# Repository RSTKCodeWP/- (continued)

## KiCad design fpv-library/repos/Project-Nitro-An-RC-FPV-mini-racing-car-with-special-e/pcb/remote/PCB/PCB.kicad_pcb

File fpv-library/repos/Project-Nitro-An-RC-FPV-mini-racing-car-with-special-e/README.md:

# Project-Nitro 🏎️💨

### FPV RC Racing Car with Game Effects

Have you ever wondered about having a **FPV RC Racing Car** with game effects such as:
- Boost
- Gun
- Health
- Drift (Bad effects and more)

Well, I have made this with the help of **NFC TAGS**. How it works is simple: when each car has an NFC reader underneath, and when it passes over a NFC tag, it will detect the code and look for what power or bad effect it is. Then I can pull that effect whenever we want. Beat your opponent and win with super powers using our own strategy to win the game!

## Zine
[zine](/doc/zine.pdf)

## Hardware Showcase 🛠️
### Photos of Car and Remote 📸

#### Car 

#### Remote

### Circuit & Diagram

#### Car Schematics

#### Remote PCB & Schematics

## Motivation

I have always wondered to play **RC car** like in games with boost, power, win, health etc.. because that all make more fun for the world and playing with friends makes it even more fun. So I built this car - it will give you a game vibe with RC FPV cars in real life, bringing more fun and joy to the world!
## How to Build 🛠️

### Car Assembly

After 3D printing, check the tolerance of each part and sand it smoothly for better look and placement. Then solder everything with wires, place each component in its designated position as shown in the `.step` files, glue the IR receiver and transmitter, tape or glue the batteries in their places, place ESP32 on the ESP tray and screw it well, then mount to the car body as shown.
## Car Assembly

1. 3D print all STL files from `/cad/car`.
2. Sand the parts until they fit smoothly.
3. Insert all M3 heat inserts
4. Mount the N20 motor using two M3 screws.
5. Install the steering servo.
6. Mount the ESP32.
7. Install the PN532 NFC module.
8. Connect all electronics according to wiring diagram.
9. Mount FPV cam.
10. Install battery
11. scraw body

### Remote Assembly
## Car Assembly

1. 3D print all STL files from `/cad/remote`.
2. Sand the parts until they fit smoothly.
3. Insert all M3 heat inserts.
4. place the batter.
5. Mound the ESP32.
6. Mount PCB after soldering all switchs and LED.
7. Insert the button.
8. Connect all electronics according to wiring diagram.
9. Slide in the sreen and screw.
10. Slide the bottom case.
11. Close body.

After 3D printing, check the tolerance of each part and sand it smoothly for better look and placement. Then solder everything with wires, place the battery first followed by ESP32, solder the switch to PCB and connect the GPIOs Don't forget to place the LCD screen holders to screw for better holding, slide down the bottom part and screw it also then paint everything.

## How to Play/Setup 🎮

When you turn on the remote and car, it will connect (if it's your first time,you may need to pair them) You'll get a web interface in phone or laptop for FPV. Once connected you have two modes:

### Free Ride Mode
You can drive it as normal RC car without any special features.

### Race Mode  
In this mode, you need an opponent to play with. One of you will host the game and that person's car becomes the controller of the game also. The remote looks for players  when a player is found:
- Flip the car and reegister all NFC tags again
- Accept the win gate tag and pit lane
- Place everthing in place as you want
- Everywhere, you can make your own track with anything you have
- Play and win the game
## Game Effects ⚡

### Good Power-ups
- **Boost** - Speed boost to move faster  
- **Health** - Get more health  
- **Shield** - Protection from enemy bullets  
- **Bullets** - Shoot projectiles  

### Bad Effects
- **Drift** - The car gets drift randomly  
- **Random Control** - Controls switch randomly (forward becomes backward)  
- **Slowness** - Car goes slowly  
- **Damage** - Low health  

### Bonus Feature
All bad effects can be cleared by going to your own pit lane.
## How It Works ⚙️

This all works with ESP-NOW protocol. The host's car maintains the rules and everything:

- `car ↔ remote` - Direct communication between each unit  
- `car(host) ↔ car(client)` - Host communicates with client cars  
- `camera → WiFi web → phone, laptop...` - Video stream to viewer devices

## Folder Structure 📁
```
cad/

├── car/
│   └── car.step

├── remote/
│   └── Remote.step

├── nfc/
│   └── nfc tag sticker.step

firmware/

├── car/
│   └── Car firmware

├── remote/
│   └── Remote firmware

├── camera/
│   └── FPV camera firmware
```

### Car Section
- [Car CAD](/cad/car/) - 3D models and designs  
- [Car Firmware](/firmware/car/) - Embedded code for the Car  
- [FPV Camera](/firmware/car_cam/) - Camera firmware  
- [Car Circuit](/circuit/car/) - Schematic diagrams  

### Remote Section
- [Remote CAD](/cad/remote/) - 3D models and designs  
- [Remote Firmware](/firmware/remote/) - Embedded code for the remote  
- [Remote circuit](/circuit/remote/) - Schematic diagrams

## BOM (Bill of Material)
[BOM](/doc/BOM.csv.csv)

## Car Components 🛒

|**Item**|Number|Approx. Price|Link|
|--------|-------------|-------------|---|
|5mm 940nm IR Emitter Transmitter|2|₹140|[Amazon](https://amzn.in/d/03gj3whx)|
|MPU6050 IMU|1|₹174|[Amaz](https://amzn.in/d/0gS9H64g)|
|PN532 NFC RFID Module|1|₹425|[Robokit](https://robokits.co.in/wireless-solutions/rfid/pn532-nfc-rfid-module-v3-kit-reader-writer-breakout-board?srsltid=AfmBOooBJS2DFnuWBIGC9mB0mO7za8Ql3MFEb6kDh34OEwg5jFQdKodmrjA)|
|ESP32S3-Sense|1|₹1800|[SeeedStudio](https://www.seeedstudio.com/XIAO-ESP32S3-Sense-p-5639.html?srsltid=AfmBOooVpv6VY6S8HZ8RSQHJR3o-OCpF9PW-xqElodKlTDqwqZxqCzhl)|
|ESP32 WiFi Bluetooth|1|₹299|[Amazon](https://amzn.in/d/0fkaqaUV)|
|6V N20 600 RPM Motor|1|₹149|[Robocraz](https://robocraze.com/products/6v-n20-600-rpm-miniature-gear-motor)|
|3.7V 2500mAh 18650 Li-Ion Battery|2|₹500|[Robocraze](https://robocraze.com/products/3-7v-2500mah-18650-li-ion-battery)|
|TP4056 Type-C Mini Charger|1|₹49|[Robocraz](https://robocraze.com/products/tp4056-battery-charger-c-type-module-with-protection-1)|
|LM2596 DC-DC Buck Converter|1|₹79|[Robocraze](https://robocraze.com/products/lm2596-dc-dc-buck-module)|
|SG90 Micro Servo Motor|1|₹99|[robocraze](https://robocraze.com/products/sg90-micro-servo-motor)|
|DRV8833 2-Channel Driver|1|₹99|[Robocraze](https://robocraze.com/products/drv8833-2-channel-dc-motor-driver)|
|TSOP38238 IR Receiver Diode|2|₹50|[QuartzComponents](https://quartzcomponents.com/products/tsop38238-ir-receiver-diode-38khz)|
|M3x4mm Heat Set Inserts|20|₹80|[Robu](https://robu.in/product/m3-x-4-mm-brass-heat-set-knurl-threaded-round-insert-nut-25-pcs/)|
|M3 x 6mm Screw|20|₹60|[RoboticsDNA](roboticsdna.in/product/m3-x-6mm-bolt-ss-304-csk-countersunk-philips-head-25-pcs/)|

#### Approximate Car Cost: **₹4,000**

### Remote

|**Item**|Number|Approx. Price|Link|
|--------|-----|-------------|---|
|ESP32 WiFi Bluetooth|1|₹299|[Amazon](https://amzn.in/d/03HUoLg3)|
|Tactile momentary push button|12|₹36|[amazon](https://amzn.in/d/093r9Vyk)|
|3.7V 1500mAh LiPo Rechargeable Battery Model|1|₹350|[robocraze](https://robocraze.com/products/3-7v-1500mah-lipo-rechargeable-battery-model-uk-523450p?_pos=1&_sid=d113ab62b&_ss=r)|
|TP4056 Type-C Mini|1|₹49|[robocraze](https://robocraze.com/products/tp4056-battery-charger-c-type-module-with-protection-1)|
|3.3V Small Piezo Buzzer|1|₹30|https://robocraze.com/products/3-volts-buzzer-small|
|5mm Common Anode RGB LED 4Pin Through Hole White Diffused LED|1|₹15|[robocraze](https://robocraze.com/products/5mm-common-anode-rgb-led-4pin-pack-of-10)|
|2.8 Inch TFT LCD Display|1|₹780|[robocraze](https://robocraze.com/products/smartelex-2-8-inch-tft-lcd-display-240x320-color-lcd-screen-for-diy-electronics)|
|m3x4mm heat set inserts|12|₹80|[Rubu](https://robu.in/product)|m3-x-4-mm-brass-heat-set-knurl-threaded-round-insert-nut-25-pcs/|
|M3 x 6mm screw|12|₹60|[RoboticsDNA](roboticsdna.in/product/m3-x-6mm-bolt-ss-304-csk-countersunk-philips-head-25-pcs/)
#### Approximate Remote Cost
**₹1700**

### Total Approximate Cost

|Part|Cost|
|-----|-----|
|Car|₹4000|
|Remote|₹1700|

# Future Upgrade ⏫

* Leader Board 
* Anti-Cheat
* challenge etc

Thats it for now.
> **NOTE:** you need to place a black transparent plastic thin sheet or something on the front window where the camera is placed and in the remote for the switch you can either use this Prototyping PCB or you can custom print a pcb board everything on car and remote is either snap fit or screwable and only the led , ir and batter need glue-gun/tap

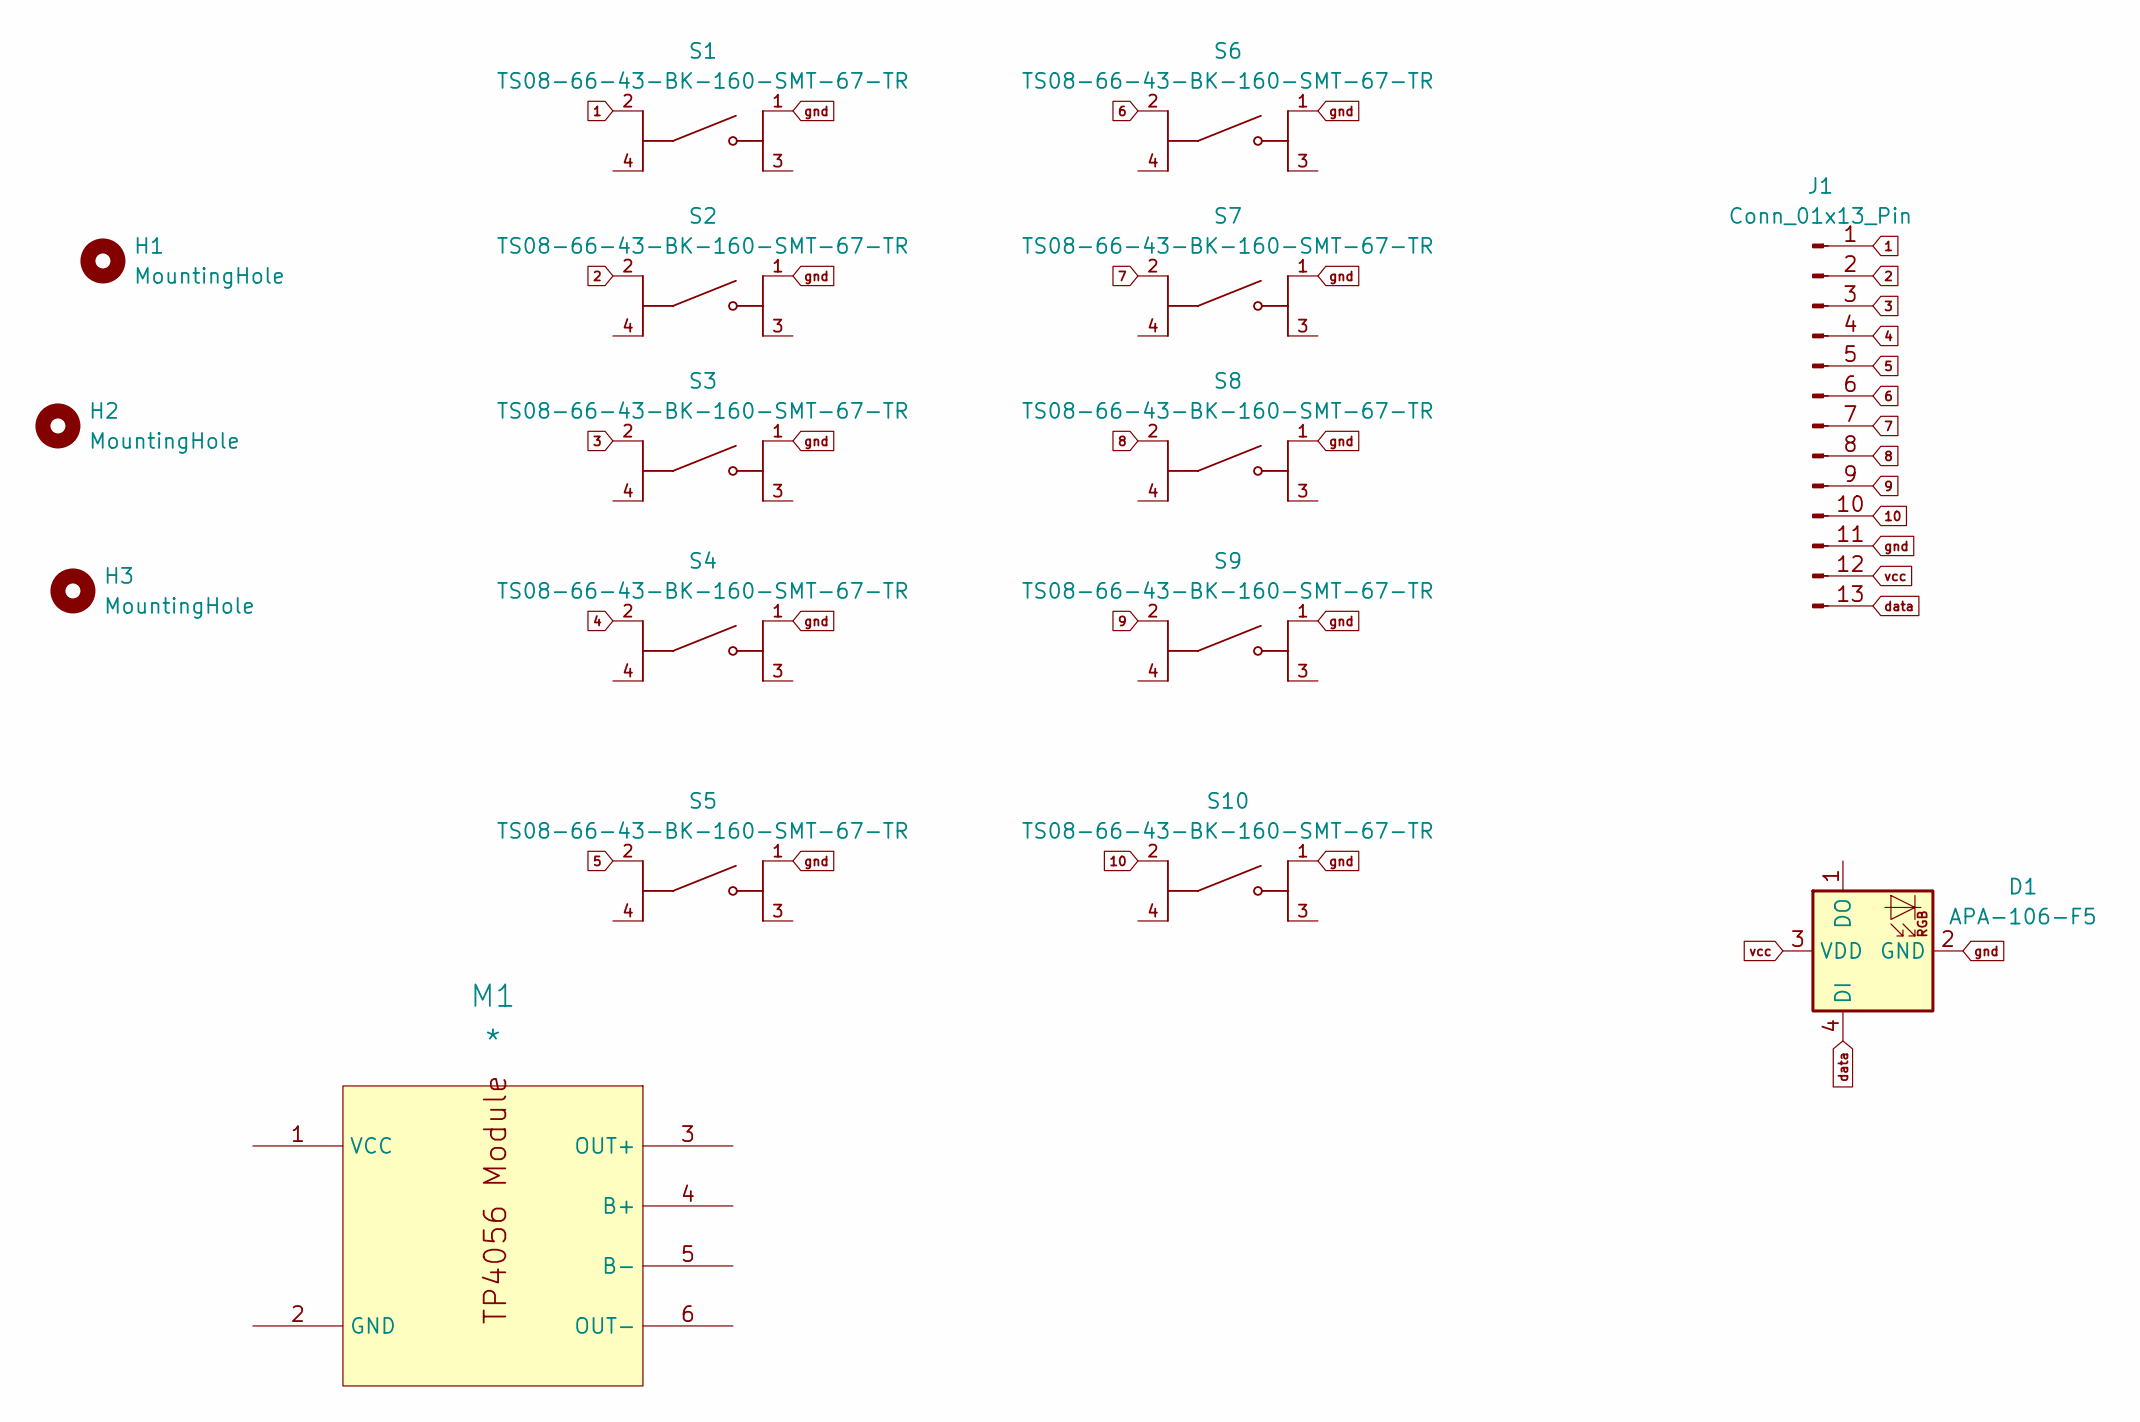
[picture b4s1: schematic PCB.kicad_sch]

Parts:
D1: APA-106-F5; LED_D5.0mm-4_RGB
H1, H2, H3: MountingHole; MountingHole_3mm
J1: Conn_01x13_Pin; PinSocket_1x13_P2.00mm_Horizontal
M1: *; tp4056
S1, S2, S3, S4, S5, S6, S7, S8, S9, S10: TS08-66-43-BK-160-SMT-67-TR; SW_PUSH_6mm; PARTREV 1.03

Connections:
1: J1.1, S1.2
2: J1.2, S2.2
3: J1.3, S3.2
4: J1.4, S4.2
5: J1.5, S5.2
6: J1.6, S6.2
7: J1.7, S7.2
8: J1.8, S8.2
9: J1.9, S9.2
10: J1.10, S10.2
data: D1.4 (DI), J1.13
gnd: D1.2 (GND), J1.11, S1.1, S2.1, S3.1, S4.1, S5.1, S6.1, S7.1, S8.1, S9.1, S10.1
vcc: D1.3 (VDD), J1.12

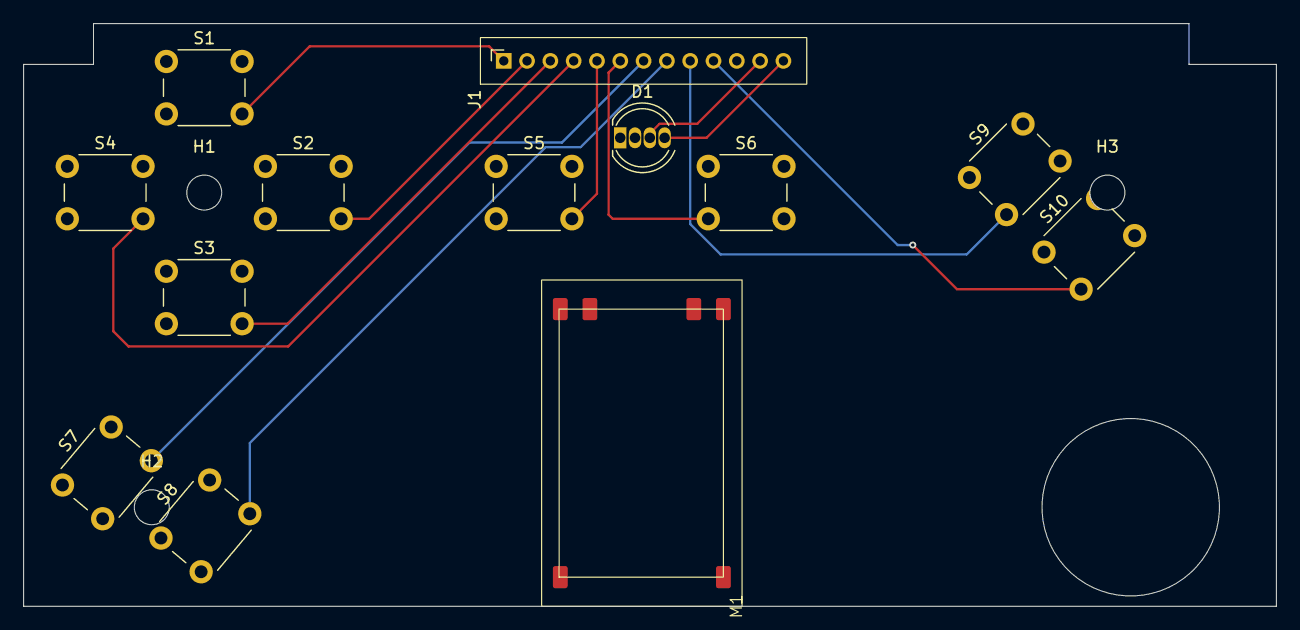
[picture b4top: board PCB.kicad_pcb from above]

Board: 2 copper layers, 107.5 x 50.0 mm, 16 parts (0 on the bottom side), 13 nets.

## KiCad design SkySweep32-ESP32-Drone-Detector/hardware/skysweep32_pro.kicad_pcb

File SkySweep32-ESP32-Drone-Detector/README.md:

# SkySweep32 | Пассивный детектор БПЛА

**Multi-band passive drone detector | Мультидиапазонный пассивный детектор дронов**

[English](#english) | [Русский](#russian)

---

## 🇬🇧 English

### Overview

SkySweep32 is an advanced passive drone detection system based on the ESP32 microcontroller. It monitors radio spectrum across three frequency bands (900 MHz, 2.4 GHz, 5.8 GHz) to detect UAV control signals and video transmission. **Built with a modular, budget-friendly architecture** — start with a ~$15 base kit and upgrade as needed.

### 📦 Modular Tiers

| Tier | Name | Cost | Includes |
|------|------|------|----------|
| 🟢 **Base** | Starter | ~$15-20 | ESP32 + OLED + NRF24L01+ (2.4 GHz) + Web Dashboard + BLE Remote ID |
| 🟡 **Standard** | Hunter | ~$35-45 | Base + CC1101 (900 MHz) + RX5808 (5.8 GHz) + ML Classification |
| 🔴 **Pro** | Sentinel | ~$60-80 | Standard + GPS + SD Card Logger + LoRa Mesh Network |
| 🟣 **EW Mode** | Juggernaut | ~$100+ | Sentinel + 4x VCO Jamming Modules (5.8G, 2.4G, 900M, 1.5G) |

**Optional add-ons**: 🎤 Acoustic Detection (~$5) | ⚔️ Countermeasures (auth required)

> 📖 **[Full Modular Guide →](docs/en/modules.md)**

### Features

- **Multi-band RF & Spectrum Scanning**: Hardware sweeping across 900 MHz, 2.4 GHz, and 5.8 GHz bands checking for analog and digital drone links.
- **Web Dashboard & Map**: Real-time dark-themed dashboard via WiFi with Leaflet.js interactive map, drone lists, and RSSI graphs.
- **Signal Fingerprinting**: Built-in `SignalDatabase` identifying known drone patterns (e.g., DJI OcuSync, FPV Analog, Crossfire) via band-matching and RSSI variance.
- **ESP-NOW Mesh**: Free, autonomous node-to-node network sharing threat alerts, heartbeats, and GPS telemetry across massive areas without extra hardware.
- **Power Management**: 4 dynamic power states (Full, Balanced, Low, Deep Sleep) with battery ADC monitoring and runtime estimates.
- **Countermeasures (Juggernaut)**: Optional VCO signal injection covering DJI, Walksnail, OpenIPC, ELRS, and GPS Denial.
- **ATAK Integration (Cursor on Target)**: Native UDP broadcast of CoT packets to the Android Team Awareness Kit, showing drone targets and operator heading on tactical maps.
- **Hardware Compass (QMC5883L)**: Direction finding via I2C magnetometer, calculating the vector of incoming drone signals.
- **TinyML AI Classification**: TensorFlow Lite for Microcontrollers engine for predicting drone classes (DJI, FPV, etc.) based on RSSI variance and multi-band tensors.
- **Stealth Mode (Dark Mode)**: Hardware/Software toggle to instantly disable OLED and buzzers, transferring all alerts to a covert vibration motor.
- **Auto-Calibration Tool**: Integrated baseline noise calibration directly from the Web-UI.
- **Alert System**: Non-blocking intelligent Buzzer and LED patterns scaling with Threat Levels (Info → Critical).
- **Remote ID**: FAA ANSI/CTA-2063 compliant BLE drone identification natively on the ESP32.
- **FreeRTOS Architecture**: Safe concurrent processing with hardware Watchdogs and SPI mutexes.

### Hardware Components (Standard Tier)

| Component | Model | Frequency | Purpose |
|-----------|-------|-----------|---------| 
| Microcontroller | ESP32 DevKit | - | Main processor + WiFi + BLE |
| RF Module 1 | CC1101 | 900 MHz | ISM band monitoring |
| RF Module 2 | NRF24L01+ | 2.4 GHz | WiFi/RC monitoring |
| RF Module 3 | RX5808 | 5.8 GHz | Video link monitoring |
| Display | OLED 128x64 (I2C) | - | Visual interface |
| Microphone (optional) | ICS-43434 MEMS | I2S | Acoustic detection |

> 🛠️ **Ready to Build?**
> See the [PCB Assembly Guide (Pro Tier)](docs/en/pcb_assembly.md) for full BOM, KiCad files, and soldering instructions.
> Looking for a case? We have official FreeCAD/STL designs in the [Enclosures Guide](docs/en/enclosures.md).

### Pinout Configuration (Conflict-Free)

#### SPI Bus (Shared)
| Signal | ESP32 Pin |
|--------|-----------|
| MOSI   | GPIO 23   |
| MISO   | GPIO 19   |
| SCK    | GPIO 18   |

#### Chip Select Pins
| Module      | CS Pin    | CE Pin | Tier |
|-------------|-----------|--------|------|
| NRF24L01+   | GPIO 15   | GPIO 2 | Base+ |
| CC1101      | GPIO 5    | -      | Standard+ |
| RX5808      | GPIO 13   | -      | Standard+ |
| LoRa SX1276 | GPIO 14   | -      | Pro (Changed in v0.4) |
| SD Card     | GPIO 27   | -      | Pro |

#### EW Output Pins (Juggernaut)
| Signal | ESP32 Pin | Purpose |
|--------|-----------|---------|
| DAC 1  | GPIO 25   | 5.8GHz / 2.4GHz VCO Sweep |
| DAC 2  | GPIO 26   | 900MHz / 1.5GHz GPS VCO Sweep |
| LORA_R | GPIO 12   | LoRa Reset moved here |

#### I2C Bus (OLED Display)
| Signal | ESP32 Pin |
|--------|-----------|
| SDA    | GPIO 21   |
| SCL    | GPIO 22   |

#### Additional Connections
- **RX5808 RSSI**: GPIO 34 (ADC1_CH6)
- **Power**: 3.3V and GND to all modules

### Software Architecture

```
src/
├── main.cpp                    # FreeRTOS tasks & app orchestration
├── config.h                    # Central config: tiers, pins, feature flags
├── config_manager.h/cpp        # Runtime JSON config (SPIFFS)
├── spi_manager.h/cpp           # Thread-safe shared-SPI bus (mutex)
├── power_manager.h/cpp         # Power modes, battery ADC, deep sleep
├── alert_manager.h/cpp         # Non-blocking buzzer/LED alert patterns
├── countermeasures.h/cpp       # Threat assessment + optional EW (Juggernaut)
├── signal_database.h/cpp       # Drone signal fingerprinting
├── espnow_mesh.h/cpp           # ESP-NOW node-to-node mesh alerts
├── web_server.h/cpp            # WiFi AP, dashboard, REST + WebSocket
├── remote_id_detector.h/cpp    # BLE Remote ID scanner
├── ml_classifier.h/cpp         # Drone classification (rules + TFLite)
├── model_data.h                # TinyML model blob
├── gps_module.h/cpp            # GPS (NEO-6M/7M)            [Pro]
├── data_logger.h/cpp           # SD-card forensic logging   [Pro]
├── meshtastic_client.h/cpp     # LoRa mesh + trilateration  [Pro]
├── atak_client.h/cpp           # ATAK Cursor-on-Target UDP  [optional]
├── compass_module.h/cpp        # QMC5883L direction finding [optional]
├── acoustic_detector.h/cpp     # I2S MEMS acoustic detection[optional]
├── drivers/
│   ├── cc1101.h/cpp            # CC1101 900 MHz driver
│   ├── nrf24l01.h/cpp          # NRF24L01+ 2.4 GHz driver
│   └── rx5808.h/cpp            # RX5808 5.8 GHz driver
└── protocols/
    ├── mavlink_parser.h/cpp    # MAVLink protocol decoder
    └── crsf_parser.h/cpp       # CRSF/ExpressLRS decoder

test/host/                      # Desktop unit tests (g++ + ASan/UBSan)
```

### Build Instructions

```bash
# Clone repository
git clone https://github.com/bobberdolle1/SkySweep32.git
cd SkySweep32

# Build firmware
pio run

# Upload to ESP32
pio run --target upload

# Monitor serial output
pio device monitor
```

### Testing

The protocol parsers (CRSF/MAVLink), which decode untrusted over-the-air input, have
desktop unit tests that build with the host `g++` — no ESP32 toolchain required:

```bash
make -C test/host      # builds with AddressSanitizer/UBSan and runs the suite
```

These run in CI (`.github/workflows/host-tests.yml`) alongside a `cppcheck`
static-analysis pass. See [`test/host/README.md`](test/host/README.md).

### Configuration

#### Enable Countermeasures (REQUIRES LEGAL AUTHORIZATION)

Edit `platformio.ini`:
```ini
build_flags = -DENABLE_COUNTERMEASURES
```

Edit `src/main.cpp`:
```cpp
counterMeasures.armSystem(true);  // Uncomment this line
```

### Legal Notice

⚠️ **WARNING**: Active RF countermeasures (jamming, protocol injection) are **ILLEGAL** in most jurisdictions without explicit authorization from regulatory authorities. Use of these features may result in:

- Criminal prosecution
- Heavy fines
- Equipment confiscation
- Interference with critical communications

**Authorized Use Cases**:
- Military and law enforcement operations
- Critical infrastructure protection (with permits)
- Conflict zones with appropriate authorization
- Research and development in controlled environments

**This project is for educational and authorized defense purposes only.**

### Documentation

- 🍼 **[Absolute Beginner Guide (Start Here)](docs/en/start_from_zero.md)** — No soldering, Lego-style assembly for beginners
- 📘 [Hardware Setup Guide](docs/en/hardware.md) — Advanced wiring & BOM
- 💻 [Software API Reference](docs/en/software.md) — REST & WebSocket APIs
- ⚖️ [Legal Compliance](docs/en/legal.md) — Responsible use

### License

GNU General Public License v3.0 - See [LICENSE](LICENSE) file for details.

---

## 🇷🇺 Русский

### Обзор

SkySweep32 — продвинутая система пассивного обнаружения дронов на базе микроконтроллера ESP32. Система мониторит радиоэфир в трех диапазонах (900 МГц, 2.4 ГГц, 5.8 ГГц) для детекции сигналов управления БПЛА и видеопередачи. Включает опциональные возможности активного противодействия для авторизованных оборонных применений.

### Возможности

- **Мультидиапазонное и Спектральное сканирование**: Аппаратный скан эфира на 900 МГц, 2.4 ГГц и 5.8 ГГц диапазонах для детекции пультов, телеметрии и видеолинков.
- **Web-Дашборд и Интерактивная Карта**: Локальный веб-интерфейс по WiFi с картой (Leaflet.js) для трекинга дронов и операторов через Remote ID.
- **Сигнатурная База (Fingerprinting)**: Динамическое распознавание 8 типов дронов (DJI OcuSync, FPV, Crossfire и др.) через анализ дисперсии RSSI и паттернов "прыжков".
- **Своя Mesh-сеть (ESP-NOW)**: Самоорганизующаяся децентрализованная сеть оповещения между детекторами (0 рублей стоимости, использует WiFi чип ESP32).
- **Активный РЭБ (Juggernaut)**: Управление каскадом из 4-х внешних VCO-генераторов (5.8GHz, 2.4GHz, 900MHz, 1.5GHz GPS) через DAC-пины для подавления DJI, Walksnail, BetaFPV, OpenIPC и ELRS.
- **Power Management (Батарея)**: Глубокий сон, скалер частоты ЦП и ADC-отслеживание батареи. Позволяет работать от 18650 днями. Автоматическая калибровка шума из UI.
- **Умная Система Уведомлений**: Неблокирующий диспетчер сигналов для зуммера (Buzzer) и LED с динамическими паттернами под каждый уровень угрозы.
- **Оценка угроз**: 5-уровневая классификация (НЕТ/НИЗКАЯ/СРЕДНЯЯ/ВЫСОКАЯ/КРИТИЧЕСКАЯ).
- **Активное противодействие (опционально, требуется легальная авторизация)**.

### Компоненты (Уровень Hunter)

| Компонент | Модель | Частота | Назначение |
|-----------|--------|---------|------------|
| Микроконтроллер | ESP32 DevKit | - | Основной процессор + WiFi/BLE |
| РЧ-модуль 1 | CC1101 | 900 МГц | Мониторинг ISM-диапазона |
| РЧ-модуль 2 | NRF24L01+ | 2.4 ГГц | Спектральное сканирование / RC |
| РЧ-модуль 3 | RX5808 | 5.8 ГГц | Мониторинг видеолинка |
| Дисплей | OLED 128x64 | - | Визуальный интерфейс |
| Индикация | Passive Buzzer | - | Алерты и ошибки |

> 🛠️ **Готовы к сборке?**
> Смотрите [Руководство по сборке платы (Pro Tier)](docs/ru/pcb_assembly.md) — там полный список деталей (BOM), KiCad проекты и инструкции по пайке.
> Ищете корпус? Официальные 3D-модели (STL) и чертежи находятся в [Руководстве по корпусам](docs/ru/enclosures.md).

### Распиновка (Бесконфликтная)

#### Шина SPI (общая)
| Сигнал | Пин ESP32 |
|--------|-----------|
| MOSI   | GPIO 23   |
| MISO   | GPIO 19   |
| SCK    | GPIO 18   |

#### Пины Chip Select (индивидуальные)
| Модуль      | CS пин    | CE пин (если есть) |
|-------------|-----------|--------------------|
| NRF24L01+   | GPIO 15   | GPIO 2             |
| CC1101      | GPIO 5    | -                  |
| RX5808      | GPIO 13   | -                  |
| LoRa SX1276 | GPIO 14   | -                  |
| SD Card     | GPIO 27   | -                  |

#### Пины генерации помех (Уровень Juggernaut)
| Пин | Функция | 
|-----|---------|
| GPIO 25 | DAC 1 (Шум для 5.8GHz и 2.4GHz VCO) |
| GPIO 26 | DAC 2 (Шум для 900MHz и 1.5GHz GPS VCO) |
| GPIO 12 | LoRa RESET (перенесен с GPIO 25) |

#### Шина I2C (OLED-дисплей)
| Сигнал | Пин ESP32 |
|--------|-----------|
| SDA    | GPIO 21   |
| SCL    | GPIO 22   |

#### Дополнительные подключения (Питание и Алерты)
- **Зуммер (Buzzer)**: GPIO 4
- **LED оповещения**: GPIO 2
- **ADC Батареи (100k/100k)**: GPIO 36
- **RX5808 RSSI**: GPIO 34 (ADC1_CH6)
- **Питание**: 3.3V и GND на все модули (регулятор LDO 1117 обязателен!)

### Архитектура ПО

```
src/
├── main.cpp                    # Задачи FreeRTOS и оркестрация приложения
├── config.h                    # Центральный конфиг: уровни, пины, флаги функций
├── config_manager.h/cpp        # Runtime JSON-конфиг (SPIFFS)
├── spi_manager.h/cpp           # Потокобезопасная общая шина SPI (мьютекс)
├── power_manager.h/cpp         # Режимы питания, ADC батареи, глубокий сон
├── alert_manager.h/cpp         # Неблокирующие паттерны зуммера/LED
├── countermeasures.h/cpp       # Оценка угроз + опциональный РЭБ (Juggernaut)
├── signal_database.h/cpp       # Сигнатурная база дронов
├── espnow_mesh.h/cpp           # Mesh-оповещения ESP-NOW между узлами
├── web_server.h/cpp            # WiFi AP, дашборд, REST + WebSocket
├── remote_id_detector.h/cpp    # Сканер BLE Remote ID
├── ml_classifier.h/cpp         # Классификация дронов (правила + TFLite)
├── model_data.h                # Блоб модели TinyML
├── gps_module.h/cpp            # GPS (NEO-6M/7M)             [Pro]
├── data_logger.h/cpp           # Логирование на SD-карту     [Pro]
├── meshtastic_client.h/cpp     # LoRa mesh + трилатерация    [Pro]
├── atak_client.h/cpp           # ATAK Cursor-on-Target UDP   [опц.]
├── compass_module.h/cpp        # QMC5883L пеленгация          [опц.]
├── acoustic_detector.h/cpp     # Акустика I2S MEMS            [опц.]
├── drivers/
│   ├── cc1101.h/cpp            # Драйвер CC1101 900 МГц
│   ├── nrf24l01.h/cpp          # Драйвер NRF24L01+ 2.4 ГГц
│   └── rx5808.h/cpp            # Драйвер RX5808 5.8 ГГц
└── protocols/
    ├── mavlink_parser.h/cpp    # Декодер протокола MAVLink
    └── crsf_parser.h/cpp       # Декодер CRSF/ExpressLRS

test/host/                      # Юнит-тесты на хосте (g++ + ASan/UBSan)
```

### Инструкции по сборке

```bash
# Клонировать репозиторий
git clone https://github.com/bobberdolle1/SkySweep32.git
cd SkySweep32

# Собрать прошивку
pio run

# Загрузить на ESP32
pio run --target upload

# Мониторинг Serial
pio device monitor
```

### Тестирование

Парсеры протоколов (CRSF/MAVLink), разбирающие недоверенный ввод из эфира, покрыты
юнит-тестами, которые собираются хостовым `g++` — тулчейн ESP32 не нужен:

```bash
make -C test/host      # сборка с AddressSanitizer/UBSan и запуск тестов
```

Они гоняются в CI (`.github/workflows/host-tests.yml`) вместе со статическим
анализом `cppcheck`. Подробнее — [`test/host/README.md`](test/host/README.md).

### Конфигурация

#### Включение противодействия (ТРЕБУЕТСЯ ЛЕГАЛЬНАЯ АВТОРИЗАЦИЯ)

Редактировать `platformio.ini`:
```ini
build_flags = -DENABLE_COUNTERMEASURES
```

Редактировать `src/main.cpp`:
```cpp
counterMeasures.armSystem(true);  // Раскомментировать эту строку
```

### Правовое уведомление

⚠️ **ВНИМАНИЕ**: Активные РЧ-противодействия (глушение, инъекция протоколов) **НЕЗАКОННЫ** в большинстве юрисдикций без явного разрешения регуляторных органов. Использование этих функций может привести к:

- Уголовному преследованию
- Крупным штрафам
- Конфискации оборудования
- Помехам критическим коммуникациям

**Разрешенные случаи использования**:
- Военные и правоохранительные операции
- Защита критической инфраструктуры (с разрешениями)
- Зоны боевых действий с соответствующей авторизацией
- Исследования и разработка в контролируемых условиях

**Этот проект предназначен только для образовательных и авторизованных оборонных целей.**

### Документация

- 🍼 **[Сборка с Абсолютного Нуля (Начни отсюда)](docs/ru/start_from_zero.md)** — Никакой пайки, Лего-сборка для новичков (рядового бойца)
- 📘 [Руководство по аппаратной части](docs/ru/hardware.md) — Инструкция для инженеров с полным BOM
- 💻 [Справочник API ПО](docs/ru/software.md) — Документация REST и WebSocket
- ⚖️ [Правовое соответствие](docs/ru/legal.md) — Правила использования

### Лицензия

Стандартная общественная лицензия GNU v3.0 - См. файл [LICENSE](LICENSE) для деталей.

---

## Contributing | Вклад в проект

Contributions are welcome! Please read [CONTRIBUTING.md](CONTRIBUTING.md) for details.

Приветствуются вклады! Пожалуйста, прочитайте [CONTRIBUTING.md](CONTRIBUTING.md) для деталей.

## Support | Поддержка

- GitHub Issues: [Report bugs](https://github.com/bobberdolle1/SkySweep32/issues)
- Discussions: [Community forum](https://github.com/bobberdolle1/SkySweep32/discussions)

---

**Developed with ❤️ for drone defense research | Разработано с ❤️ для исследований противодроновой защиты**

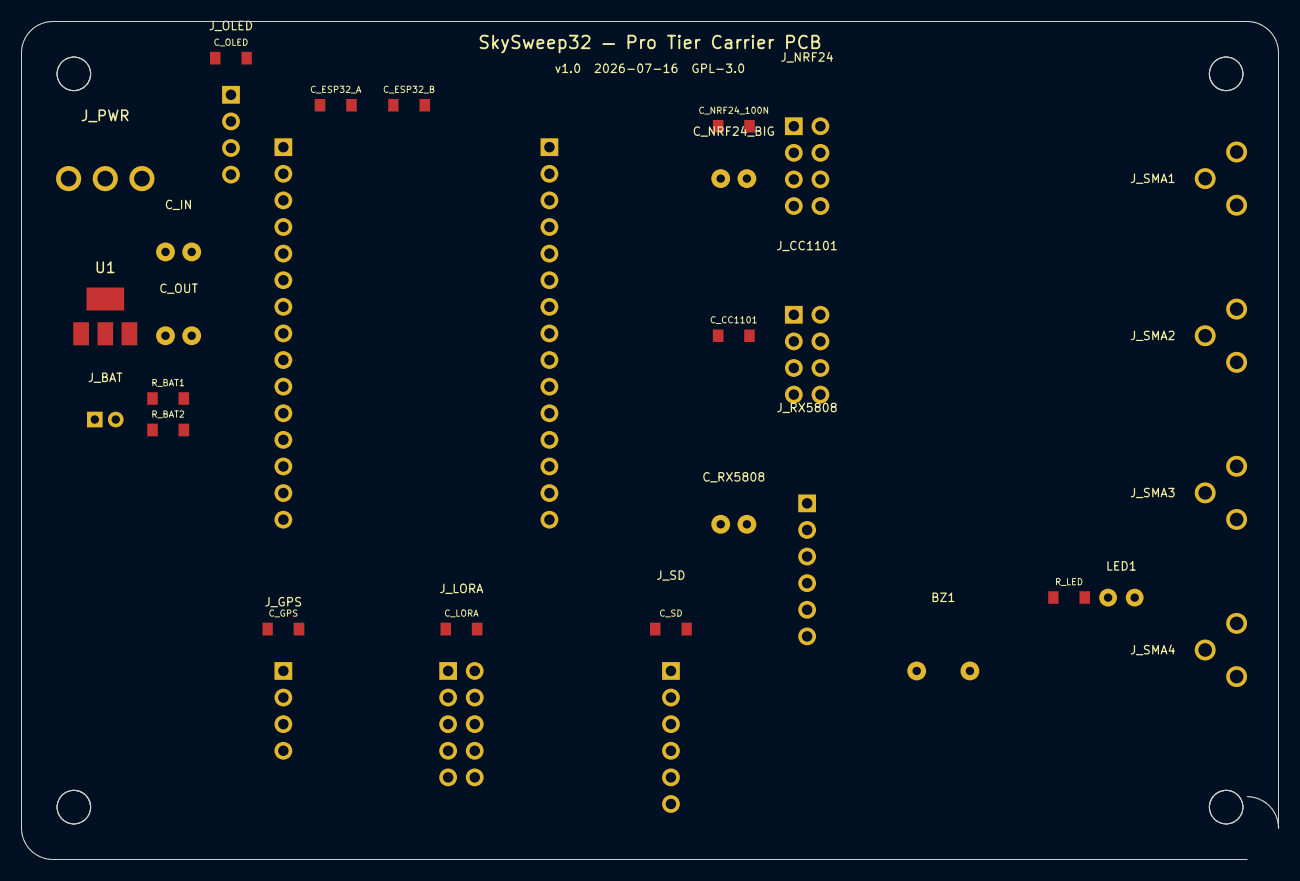
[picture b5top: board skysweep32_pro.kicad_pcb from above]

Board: 2 copper layers, 120.0 x 80.0 mm, 37 parts (0 on the bottom side), 23 nets, no tracks yet.

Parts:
BZ1: BUZZER; BZ_12x9.5mm
C_CC1101: 100nF; C_0805_2012Metric
C_ESP32_A, C_ESP32_B: 100nF; C_0805_2012Metric
C_GPS: 100nF; C_0805_2012Metric
C_IN: 100uF/16V; CP_Radial_D6.3mm_P2.50mm
C_LORA: 100nF; C_0805_2012Metric
C_NRF24_100N: 100nF; C_0805_2012Metric
C_NRF24_BIG: 10uF/10V; CP_Radial_D6.3mm_P2.50mm
C_OLED: 100nF; C_0805_2012Metric
C_OUT: 10uF/10V; CP_Radial_D6.3mm_P2.50mm
C_RX5808: 100uF/10V; CP_Radial_D6.3mm_P2.50mm
C_SD: 100nF; C_0805_2012Metric
H1, H2, H3, H4: MH_M3; MountingHole_3.2mm_M3
J_BAT: LIPO IN; JST_PH_B2B-PH-K_1x02_P2.00mm_Vertical
J_CC1101: CC1101 900MHz; PinHeader_2x04_P2.54mm_Vertical
J_ESP32_L: ESP32 Left; PinHeader_1x15_P2.54mm_Vertical
J_ESP32_R: ESP32 Right; PinHeader_1x15_P2.54mm_Vertical
J_GPS: GPS NEO-6M; PinHeader_1x04_P2.54mm_Vertical
J_LORA: LoRa SX1276; PinHeader_2x05_P2.54mm_Vertical
J_NRF24: NRF24L01+; PinHeader_2x04_P2.54mm_Vertical
J_OLED: OLED SSD1306; PinHeader_1x04_P2.54mm_Vertical
J_PWR: 5V DC IN; BarrelJack_CUI_PJ-102A_Horizontal
J_RX5808: RX5808 5.8GHz; PinHeader_1x06_P2.54mm_Vertical
J_SD: MicroSD SPI; PinHeader_1x06_P2.54mm_Vertical
J_SMA1: 900MHz CC1101; SMA_Amphenol_132289_EdgeMount
J_SMA2: 2.4GHz NRF24; SMA_Amphenol_132289_EdgeMount
J_SMA3: 5.8GHz RX5808; SMA_Amphenol_132289_EdgeMount
J_SMA4: 915MHz LoRa; SMA_Amphenol_132289_EdgeMount
LED1: LED_RED; LED_D3.0mm
R_BAT1, R_BAT2: 100k; R_0805_2012Metric
R_LED: 330R; R_0805_2012Metric
U1: AMS1117-3.3; SOT-223-3_TabPin2

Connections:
BAT_ADC: R_BAT1.2, R_BAT2.1
BAT_VRAW: J_BAT.1, R_BAT1.1
BUZZER: BZ1.1, J_ESP32_R.13
CC_CS: J_CC1101.8, J_ESP32_R.10
GND: BZ1.2, C_CC1101.2, C_ESP32_A.2, C_ESP32_B.2, C_GPS.2, C_IN.2, C_LORA.2, C_NRF24_100N.2, C_NRF24_BIG.2, C_OLED.2, C_OUT.2, C_RX5808.2, C_SD.2, J_BAT.2, J_CC1101.2, J_ESP32_L.14, J_ESP32_R.2, J_GPS.4, J_LORA.1, J_LORA.2, J_NRF24.1, J_OLED.1, J_PWR.2, J_PWR.3, J_RX5808.2, J_SD.2, J_SMA1.2, J_SMA1.3, J_SMA2.2, J_SMA2.3, J_SMA3.2, J_SMA3.3, J_SMA4.2, J_SMA4.3, LED1.2, R_BAT2.2, U1.1
GPS_RX: J_ESP32_R.12, J_GPS.3
GPS_TX: J_ESP32_R.11, J_GPS.2
I2C_SCL: J_ESP32_R.3, J_OLED.3
I2C_SDA: J_ESP32_R.4, J_OLED.4
LORA_CS: J_ESP32_L.12, J_LORA.7
LORA_DIO0: J_ESP32_L.8, J_LORA.8
LORA_DIO1: J_ESP32_L.7, J_LORA.9
LORA_RST: J_ESP32_L.13, J_LORA.10
NRF_CE: J_ESP32_R.14, J_NRF24.3, R_LED.1
NRF_CS: J_ESP32_R.15, J_NRF24.4
RX_CS: J_ESP32_L.15, J_RX5808.6
RX_RSSI: J_ESP32_L.3, J_ESP32_L.5, J_RX5808.3
SD_CS: J_ESP32_L.11, J_SD.3
SPI_MISO: J_CC1101.5, J_ESP32_R.8, J_LORA.4, J_NRF24.7, J_SD.6
SPI_MOSI: J_CC1101.3, J_LORA.5, J_NRF24.6, J_RX5808.4, J_SD.4
SPI_SCK: J_CC1101.4, J_ESP32_R.9, J_LORA.6, J_NRF24.5, J_RX5808.5, J_SD.5
VCC_3V3: C_CC1101.1, C_ESP32_A.1, C_ESP32_B.1, C_GPS.1, C_LORA.1, C_NRF24_100N.1, C_NRF24_BIG.1, C_OLED.1, C_OUT.1, C_SD.1, J_CC1101.1, J_ESP32_L.1, J_GPS.1, J_LORA.3, J_NRF24.2, J_OLED.2, J_SD.1, U1.2, U1.4
VCC_5V: C_IN.1, C_RX5808.1, J_ESP32_R.1, J_PWR.1, J_RX5808.1, U1.3

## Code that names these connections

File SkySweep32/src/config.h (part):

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// ============================================================================

// --- SPI Bus (shared by all SPI devices) ---
#define PIN_SPI_MOSI        23
#define PIN_SPI_MISO        19
#define PIN_SPI_SCK         18

// --- CC1101 (900 MHz) ---
#define PIN_CC1101_CS       5
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#define PIN_RX5808_RSSI     34    // ADC1_CH6 (analog input)

// --- OLED Display (I2C) ---
#define PIN_I2C_SDA         21
#define PIN_I2C_SCL         22

// --- GPS Module (UART2) ---
#define PIN_GPS_RX          16    // ESP32 RX ← GPS TX
#define PIN_GPS_TX          17    // ESP32 TX → GPS RX
#define GPS_BAUD_RATE       9600
#define GPS_UPDATE_INTERVAL 1000

// --- LoRa SX1276 ---
#define PIN_LORA_CS         14    // Changed from 26 (Conflicts with I2S BCLK if both are enabled)
#define PIN_LORA_DIO0       33
#define PIN_LORA_DIO1       32
#define PIN_LORA_RESET      12    // Changed from 25 (Conflicts with I2S WS if both are enabled)

// --- VCO DACs (Juggernaut) ---
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#define PIN_VCO_DAC_2       26

// --- SD Card ---
#define PIN_SD_CS           27

// --- I2S Microphone (Acoustic Detection) ---
// Note: Shares GPIO 14 and 12 with LoRa. Do not enable both MODULE_LORA and MODULE_ACOUSTIC
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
